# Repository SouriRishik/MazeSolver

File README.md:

# MazeSolver
A maze solving bot using algorithm - floodfill
The simulator used to test the robot is mackorone-mms https://github.com/mackorone/mms
Purpose of bot : Technoxian 2024
Dimensions : x n x

This bot was my first project as a part of RoboManipal. I was assigned to work on the Algorithm and its code.

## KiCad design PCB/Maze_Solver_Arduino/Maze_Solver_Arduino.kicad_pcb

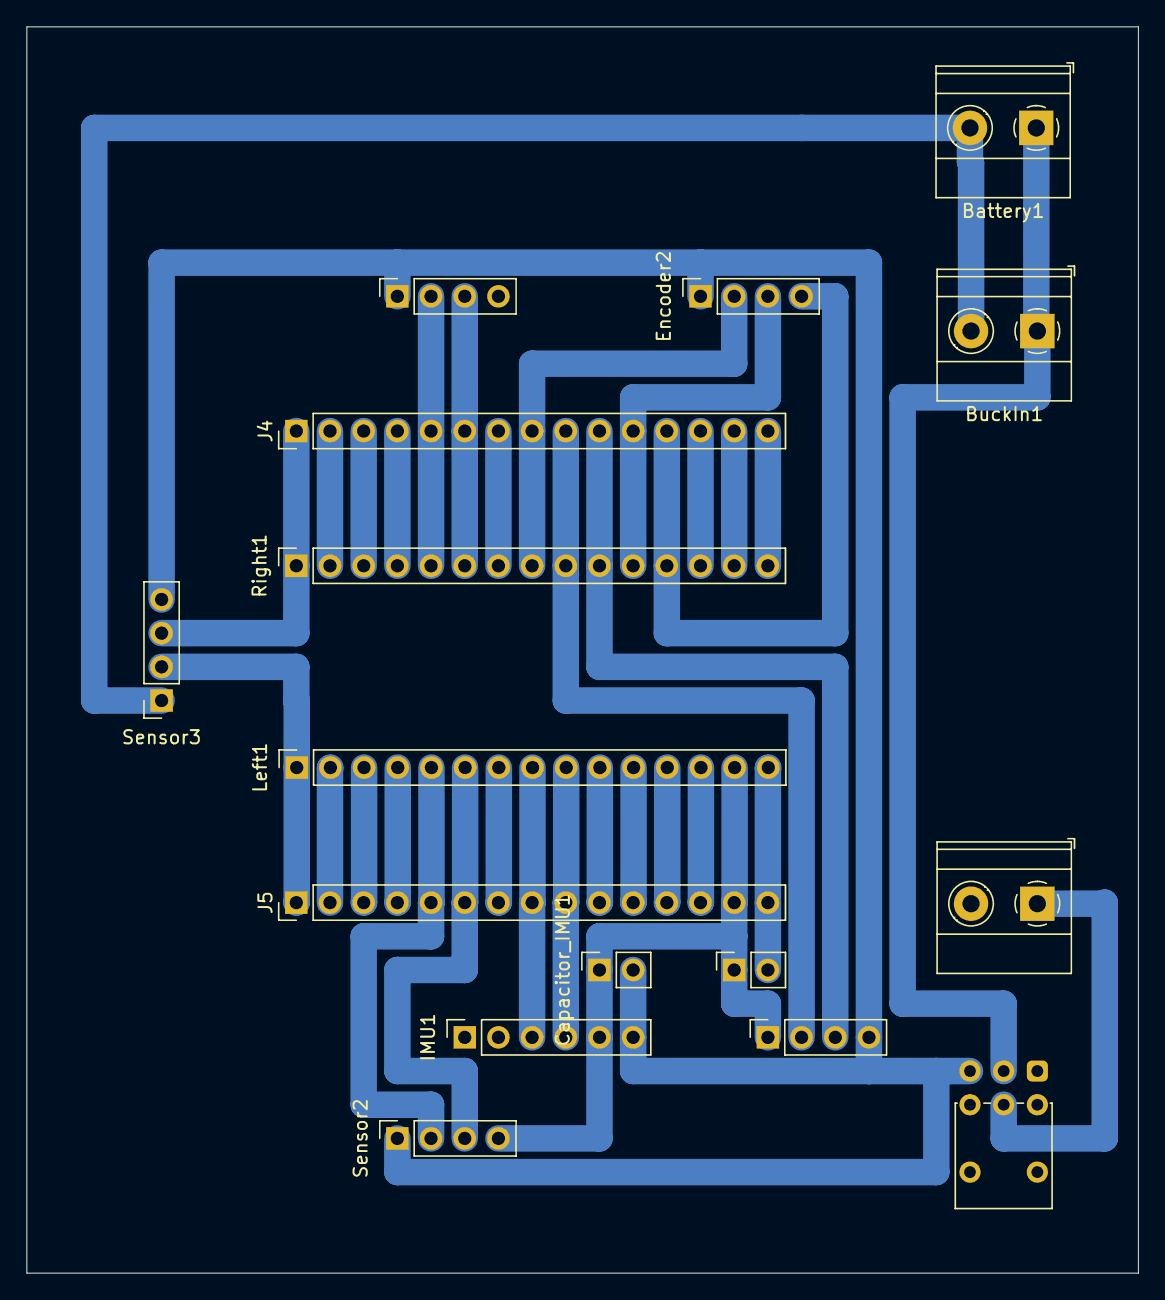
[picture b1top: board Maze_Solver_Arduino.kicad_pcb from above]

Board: 2 copper layers, 83.8 x 94.0 mm, 16 parts (0 on the bottom side), 20 nets.

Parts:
Battery1: Screw_Terminal_01x02; TerminalBlock_Phoenix_MKDS-1,5-2_1x02_P5.00mm_Horizontal
BuckIn1: Screw_Terminal_01x02; TerminalBlock_Phoenix_MKDS-1,5-2_1x02_P5.00mm_Horizontal
BuckOut1: Screw_Terminal_01x02; TerminalBlock_Phoenix_MKDS-1,5-2_1x02_P5.00mm_Horizontal
Capacitor_IMU1: Conn_01x02_Socket; PinSocket_1x02_P2.54mm_Vertical
Capacitor_Nano1: Conn_01x02_Socket; PinSocket_1x02_P2.54mm_Vertical
Encoder1, Encoder2: Conn_01x04_Socket; PinSocket_1x04_P2.54mm_Vertical
IMU1: Conn_01x06_Socket; PinSocket_1x06_P2.54mm_Vertical
J4, J5: Conn_01x15_Pin; PinHeader_1x15_P2.54mm_Vertical
KillSwitch1: SW_Push_DPDT; SW_Push_2P2T_Vertical_E-Switch_800UDP8P1A1M6
Left1: Conn_01x15_Socket; PinSocket_1x15_P2.54mm_Vertical
Right1: Conn_01x15_Socket; PinSocket_1x15_P2.54mm_Vertical
Sensor1, Sensor2, Sensor3: Conn_01x04_Socket; PinSocket_1x04_P2.54mm_Vertical

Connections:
5V: BuckOut1.1, Capacitor_Nano1.2, J5.15, KillSwitch1.5 (B), Left1.15
12V: Battery1.1, BuckIn1.1, KillSwitch1.2 (B)
E1: J4.6, Right1.6, Sensor1.3
E2: J5.6, Left1.6, Sensor2.3
E3: J5.1, Left1.1, Sensor3.2
En1A: Encoder1.3, J4.10, Right1.10
En1B: Encoder1.2, J4.9, Right1.9
En2A: Encoder2.2, J4.8, Right1.8
En2B: Encoder2.3, J4.11, Right1.11
GND: Battery1.2, BuckIn1.2, BuckOut1.2, Capacitor_IMU1.1, Capacitor_Nano1.1, Encoder1.1, Encoder2.4, IMU1.5, J4.12, J5.14, Left1.14, Right1.12, Sensor1.4, Sensor2.4, Sensor3.1
M1A: J4.2, Right1.2
M1B: J4.3, Right1.3
M2A: J4.7, Right1.7
M2B: J4.4, Right1.4
SCL: IMU1.4, J5.9, Left1.9
SDA: IMU1.3, J5.8, Left1.8
T1: J4.5, Right1.5, Sensor1.2
T2: J5.5, Left1.5, Sensor2.2
T3: J4.1, Right1.1, Sensor3.3
Vcc: Capacitor_IMU1.2, Encoder1.4, Encoder2.1, IMU1.6, KillSwitch1.3 (C), Sensor1.1, Sensor2.1, Sensor3.4

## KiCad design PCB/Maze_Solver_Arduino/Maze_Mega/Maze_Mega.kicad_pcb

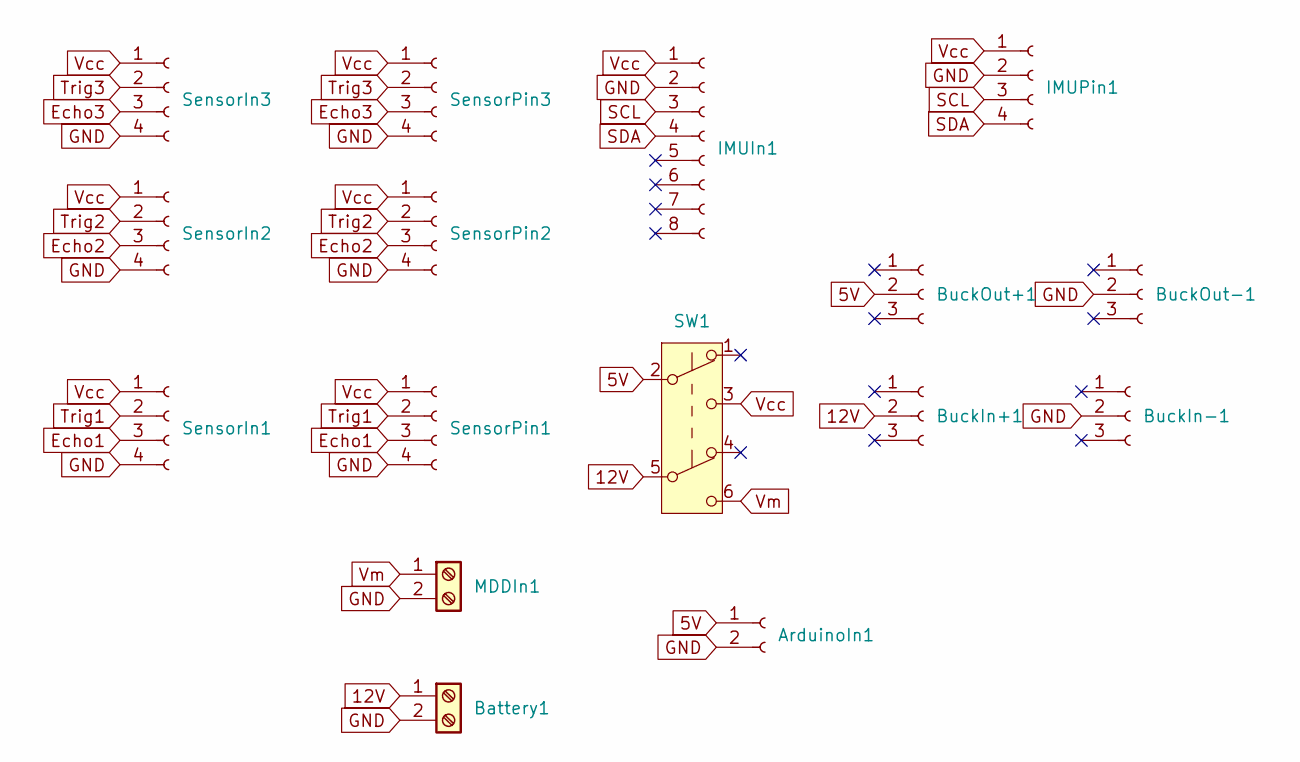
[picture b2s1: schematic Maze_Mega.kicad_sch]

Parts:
ArduinoIn1: Conn_01x02_Socket; PinSocket_1x02_P2.54mm_Vertical
Battery1: Screw_Terminal_01x02; TerminalBlock_Xinya_XY308-2.54-2P_1x02_P2.54mm_Horizontal
BuckIn+1: Conn_01x03_Socket; PinSocket_1x03_P2.54mm_Vertical
BuckIn-1: Conn_01x03_Socket; PinSocket_1x03_P2.54mm_Vertical
BuckOut+1: Conn_01x03_Socket; PinSocket_1x03_P2.54mm_Vertical
BuckOut-1: Conn_01x03_Socket; PinSocket_1x03_P2.54mm_Vertical
IMUIn1: Conn_01x08_Socket; PinSocket_1x08_P2.54mm_Vertical
IMUPin1: Conn_01x04_Socket; PinSocket_1x04_P2.54mm_Vertical
MDDIn1: Screw_Terminal_01x02; TerminalBlock_Xinya_XY308-2.54-2P_1x02_P2.54mm_Horizontal
SW1: SW_Push_DPDT; SW_Push_2P2T_Vertical_E-Switch_800UDP8P1A1M6
SensorIn1, SensorIn2, SensorIn3: Conn_01x04_Socket; PinSocket_1x04_P2.54mm_Vertical
SensorPin1, SensorPin2, SensorPin3: Conn_01x04_Socket; PinSocket_1x04_P2.54mm_Vertical

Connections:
5V: ArduinoIn1.1, BuckOut+1.2, SW1.2 (B)
12V: Battery1.1, BuckIn+1.2, SW1.5 (B)
Echo1: SensorIn1.3, SensorPin1.3
Echo2: SensorIn2.3, SensorPin2.3
Echo3: SensorIn3.3, SensorPin3.3
GND: ArduinoIn1.2, Battery1.2, BuckIn-1.2, BuckOut-1.2, IMUIn1.2, IMUPin1.2, MDDIn1.2, SensorIn1.4, SensorIn2.4, SensorIn3.4, SensorPin1.4, SensorPin2.4, SensorPin3.4
SCL: IMUIn1.3, IMUPin1.3
SDA: IMUIn1.4, IMUPin1.4
Trig1: SensorIn1.2, SensorPin1.2
Trig2: SensorIn2.2, SensorPin2.2
Trig3: SensorIn3.2, SensorPin3.2
Vcc: IMUIn1.1, IMUPin1.1, SW1.3 (C), SensorIn1.1, SensorIn2.1, SensorIn3.1, SensorPin1.1, SensorPin2.1, SensorPin3.1
Vm: MDDIn1.1, SW1.6 (C)

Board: 2 copper layers, 16 parts (0 on the bottom side), 13 nets, no tracks yet.

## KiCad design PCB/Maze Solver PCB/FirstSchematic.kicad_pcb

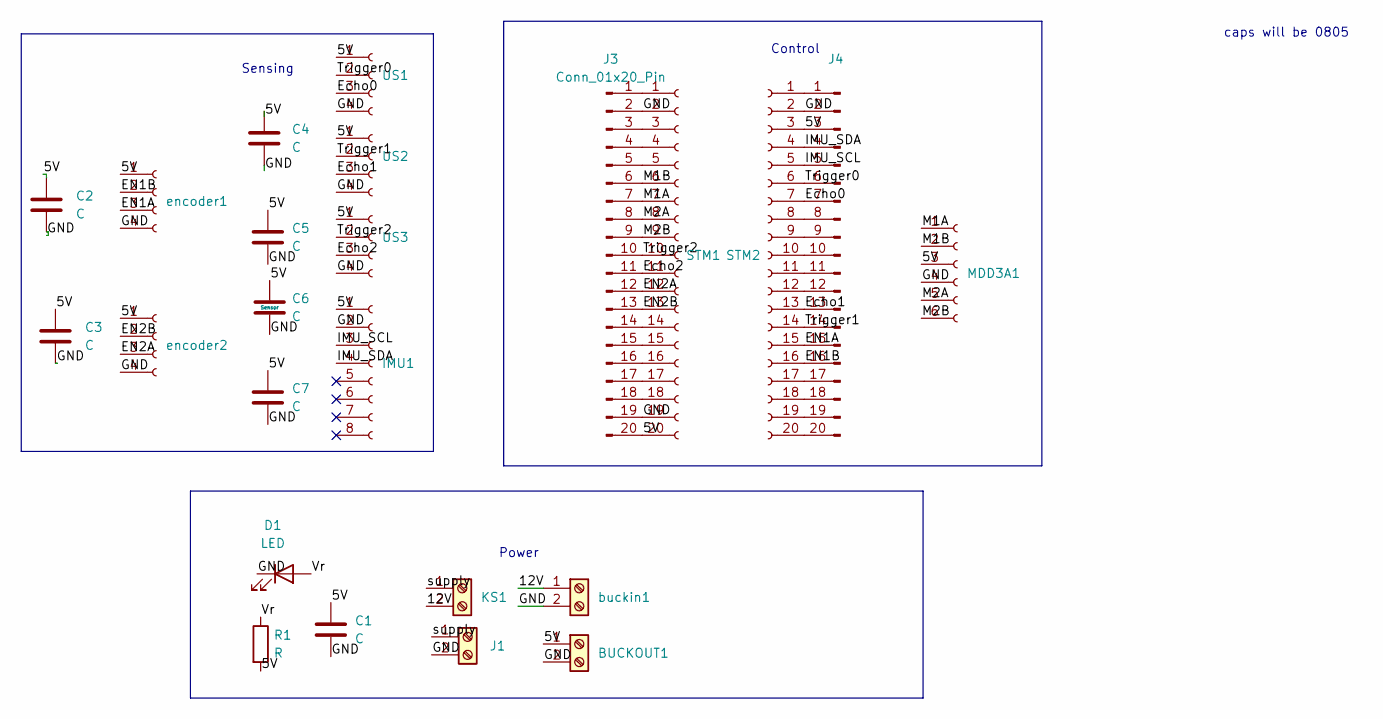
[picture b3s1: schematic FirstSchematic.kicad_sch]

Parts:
BUCKOUT1: Screw_Terminal_01x02; TerminalBlock_Xinya_XY308-2.54-2P_1x02_P2.54mm_Horizontal
C1, C2, C3, C4, C5, C6, C7: C; C_Disc_D3.0mm_W1.6mm_P2.50mm
D1: LED; LED_D3.0mm
IMU1: Conn_01x08_Socket; PinHeader_1x08_P2.54mm_Vertical
J1: Screw_Terminal_01x02; TerminalBlock_Xinya_XY308-2.54-2P_1x02_P2.54mm_Horizontal
J3, J4: Conn_01x20_Pin; PinHeader_1x20_P2.54mm_Vertical
KS1: Screw_Terminal_01x02; TerminalBlock_Xinya_XY308-2.54-2P_1x02_P2.54mm_Horizontal
MDD3A1: Conn_01x06_Socket; PinSocket_1x06_P2.54mm_Vertical
R1: R; R_Axial_DIN0207_L6.3mm_D2.5mm_P2.54mm_Vertical
STM1, STM2: Conn_01x20_Socket; PinSocket_1x20_P2.54mm_Vertical
US1, US2, US3: Conn_01x04_Socket; PinHeader_1x04_P2.54mm_Vertical
buckin1: Screw_Terminal_01x02; TerminalBlock_Xinya_XY308-2.54-2P_1x02_P2.54mm_Horizontal
encoder1, encoder2: Conn_01x04_Socket; PinHeader_1x04_P2.54mm_Vertical

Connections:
/5V: BUCKOUT1.1, C1.1, C2.1, C3.1, C4.1, C5.1, C6.1, C7.1, IMU1.1, J3.20, J4.3, MDD3A1.3, R1.2, STM1.20, STM2.3, US1.1, US2.1, US3.1, encoder1.1, encoder2.1
/12V: KS1.2, buckin1.1
/EN1A: J4.15, STM2.15, encoder1.3
/EN1B: J4.16, STM2.16, encoder1.2
/EN2A: J3.12, STM1.12, encoder2.3
/EN2B: J3.13, STM1.13, encoder2.2
/Echo0: J4.7, STM2.7, US1.3
/Echo1: J4.13, STM2.13, US2.3
/Echo2: J3.11, STM1.11, US3.3
/GND: BUCKOUT1.2, C1.2, C2.2, C3.2, C4.2, C5.2, C6.2, C7.2, D1.1 (K), IMU1.2, J1.2, J3.2, J3.19, J4.2, MDD3A1.4, STM1.2, STM1.19, STM2.2, US1.4, US2.4, US3.4, buckin1.2, encoder1.4, encoder2.4
/IMU_SCL: IMU1.3, J4.5, STM2.5
/IMU_SDA: IMU1.4, J4.4, STM2.4
/M1A: J3.7, MDD3A1.1, STM1.7
/M1B: J3.6, MDD3A1.2, STM1.6
/M2A: J3.8, MDD3A1.5, STM1.8
/M2B: J3.9, MDD3A1.6, STM1.9
/Trigger0: J4.6, STM2.6, US1.2
/Trigger1: J4.14, STM2.14, US2.2
/Trigger2: J3.10, STM1.10, US3.2
/Vr: D1.2 (A), R1.1
/supply: J1.1, KS1.1
unnamed: J3.1, STM1.1
unnamed: J3.3, STM1.3
unnamed: J3.4, STM1.4
unnamed: J3.5, STM1.5
unnamed: J3.14, STM1.14
unnamed: J3.15, STM1.15
unnamed: J3.16, STM1.16
unnamed: J3.17, STM1.17
unnamed: J3.18, STM1.18
unnamed: J4.1, STM2.1
unnamed: J4.8, STM2.8
unnamed: J4.9, STM2.9
unnamed: J4.10, STM2.10
unnamed: J4.11, STM2.11
unnamed: J4.12, STM2.12
unnamed: J4.17, STM2.17
unnamed: J4.18, STM2.18
unnamed: J4.19, STM2.19
unnamed: J4.20, STM2.20

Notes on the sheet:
Power
caps will be 0805
Control
Sensing

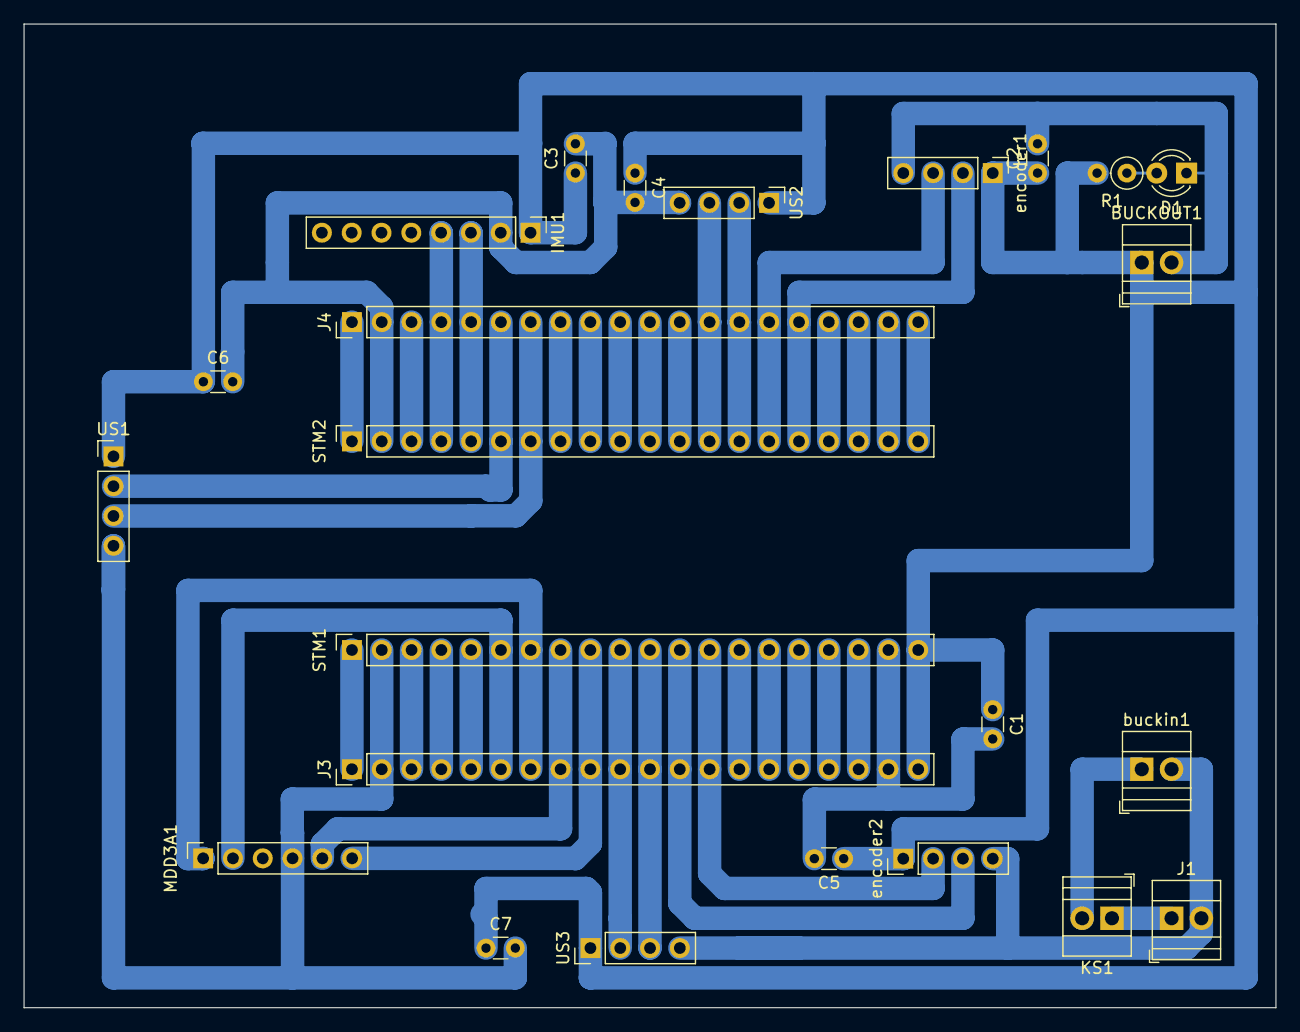
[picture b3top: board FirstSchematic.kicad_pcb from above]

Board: 2 copper layers, 106.7 x 83.8 mm, 24 parts (0 on the bottom side), 40 nets.

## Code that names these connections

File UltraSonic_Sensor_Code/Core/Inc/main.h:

/* USER CODE BEGIN Header */
/**
  ******************************************************************************
  * @file           : main.h
  * @brief          : Header for main.c file.
  *                   This file contains the common defines of the application.
  ******************************************************************************
  * @attention
  *
  * Copyright (c) 2024 STMicroelectronics.
  * All rights reserved.
  *
  * This software is licensed under terms that can be found in the LICENSE file
  * in the root directory of this software component.
  * If no LICENSE file comes with this software, it is provided AS-IS.
  *
  ******************************************************************************
  */
/* USER CODE END Header */

/* Define to prevent recursive inclusion -------------------------------------*/
#ifndef __MAIN_H
#define __MAIN_H

#ifdef __cplusplus
extern "C" {
#endif

/* Includes ------------------------------------------------------------------*/
#include "stm32f4xx_hal.h"

/* Private includes ----------------------------------------------------------*/
/* USER CODE BEGIN Includes */

/* USER CODE END Includes */

/* Exported types ------------------------------------------------------------*/
/* USER CODE BEGIN ET */

/* USER CODE END ET */

/* Exported constants --------------------------------------------------------*/
/* USER CODE BEGIN EC */

/* USER CODE END EC */

/* Exported macro ------------------------------------------------------------*/
/* USER CODE BEGIN EM */

/* USER CODE END EM */

/* Exported functions prototypes ---------------------------------------------*/
void Error_Handler(void);

/* USER CODE BEGIN EFP */

/* USER CODE END EFP */

/* Private defines -----------------------------------------------------------*/
#define LED_Pin GPIO_PIN_13
#define LED_GPIO_Port GPIOC
#define TRIG1_Pin GPIO_PIN_0
#define TRIG1_GPIO_Port GPIOA
#define TRIG2_Pin GPIO_PIN_1
#define TRIG2_GPIO_Port GPIOA
#define TRIG3_Pin GPIO_PIN_2
#define TRIG3_GPIO_Port GPIOA
#define Echo1_Pin GPIO_PIN_8
#define Echo1_GPIO_Port GPIOA
#define Echo2_Pin GPIO_PIN_9
#define Echo2_GPIO_Port GPIOA
#define Echo3_Pin GPIO_PIN_10
#define Echo3_GPIO_Port GPIOA

/* USER CODE BEGIN Private defines */

/* USER CODE END Private defines */

#ifdef __cplusplus
}
#endif

#endif /* __MAIN_H */

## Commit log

2024-08-10 Create Prog1
2024-08-10 Add files via upload
    The files for the simulator code WITH backtracking in floodfill
2024-08-10 Create WithoutBT
    Floodfill code for simulator without backtracking
2024-08-10 Add files via upload
    Floodfill code without backtracking
2024-09-29 Create UltraSonic_Sensor_Code
